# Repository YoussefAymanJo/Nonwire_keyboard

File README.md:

Nonwire_keyboard

## Description

Wireless Keyboarb based on split keyboard mechanism.As it consist of main keyboard  powered by rechargeable Battery which can operate up to week.And operated by nice Nano and soup display.The right part is Soup numpad,this numpad can operate up to week and soup friendly.
## Why it was built
I built this,beacause i always need mechanical keyboard,but i need to customize it features by myself.So this keyboard it custosmized to my needings.Also,it has customized features based on usage.Nonwire keyboard is not just regular keybaord but,desgined to be my companion.
## How to use it / Build it
Firsly,printing all 3d models after that fabricate PCB.After that assemble mx switches,MCU and battery management of pcb.then assemble all this parts together.finally,upload firmware on nice nano,the test all 
## Schematic
I made the schematic and keyboard matrix for the main keyboard, then the soup numpad the right part .

## PCB
I routed the pcb ,then i outlined the shape of keyboard and soup .

## CAD
I started   sketcking plat for main keyboard,the i the Enclosure , then the top cover.After that i worked on soup outlinne shape and assemble

 #### Soup 

## Firmware
I used kmk with circuit python as firmare,and make code for the left part which is keyboard and the right one the soup numpad

## BOM 
I made the BOM  and needed materials ,in egypt then convert its price to USD dollar.

## Zine

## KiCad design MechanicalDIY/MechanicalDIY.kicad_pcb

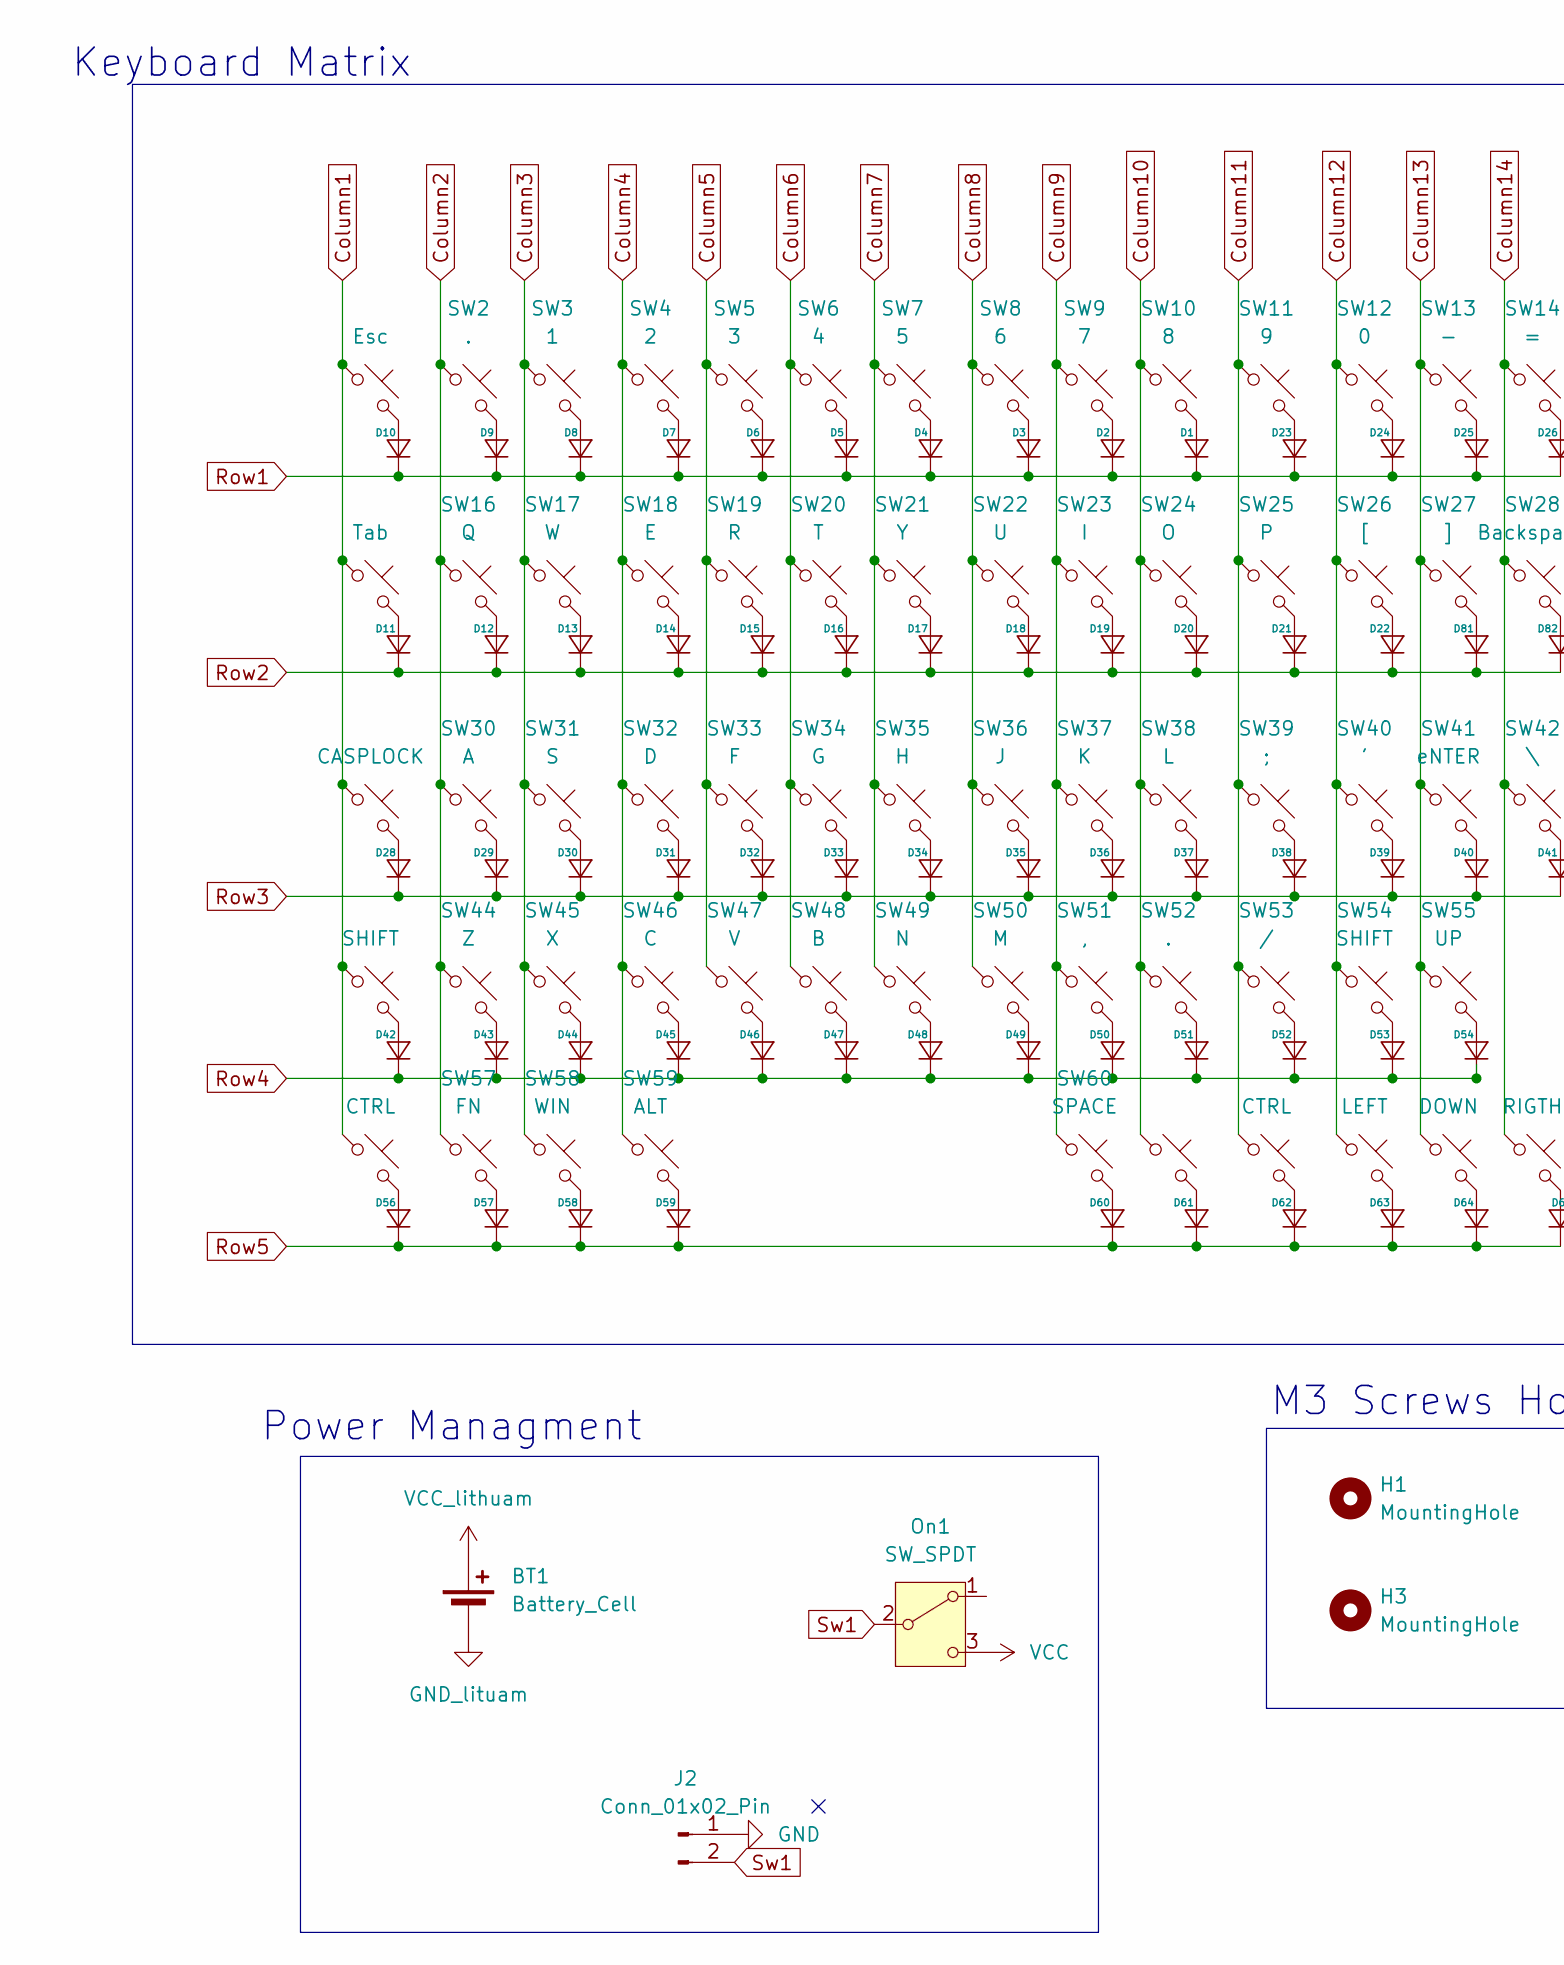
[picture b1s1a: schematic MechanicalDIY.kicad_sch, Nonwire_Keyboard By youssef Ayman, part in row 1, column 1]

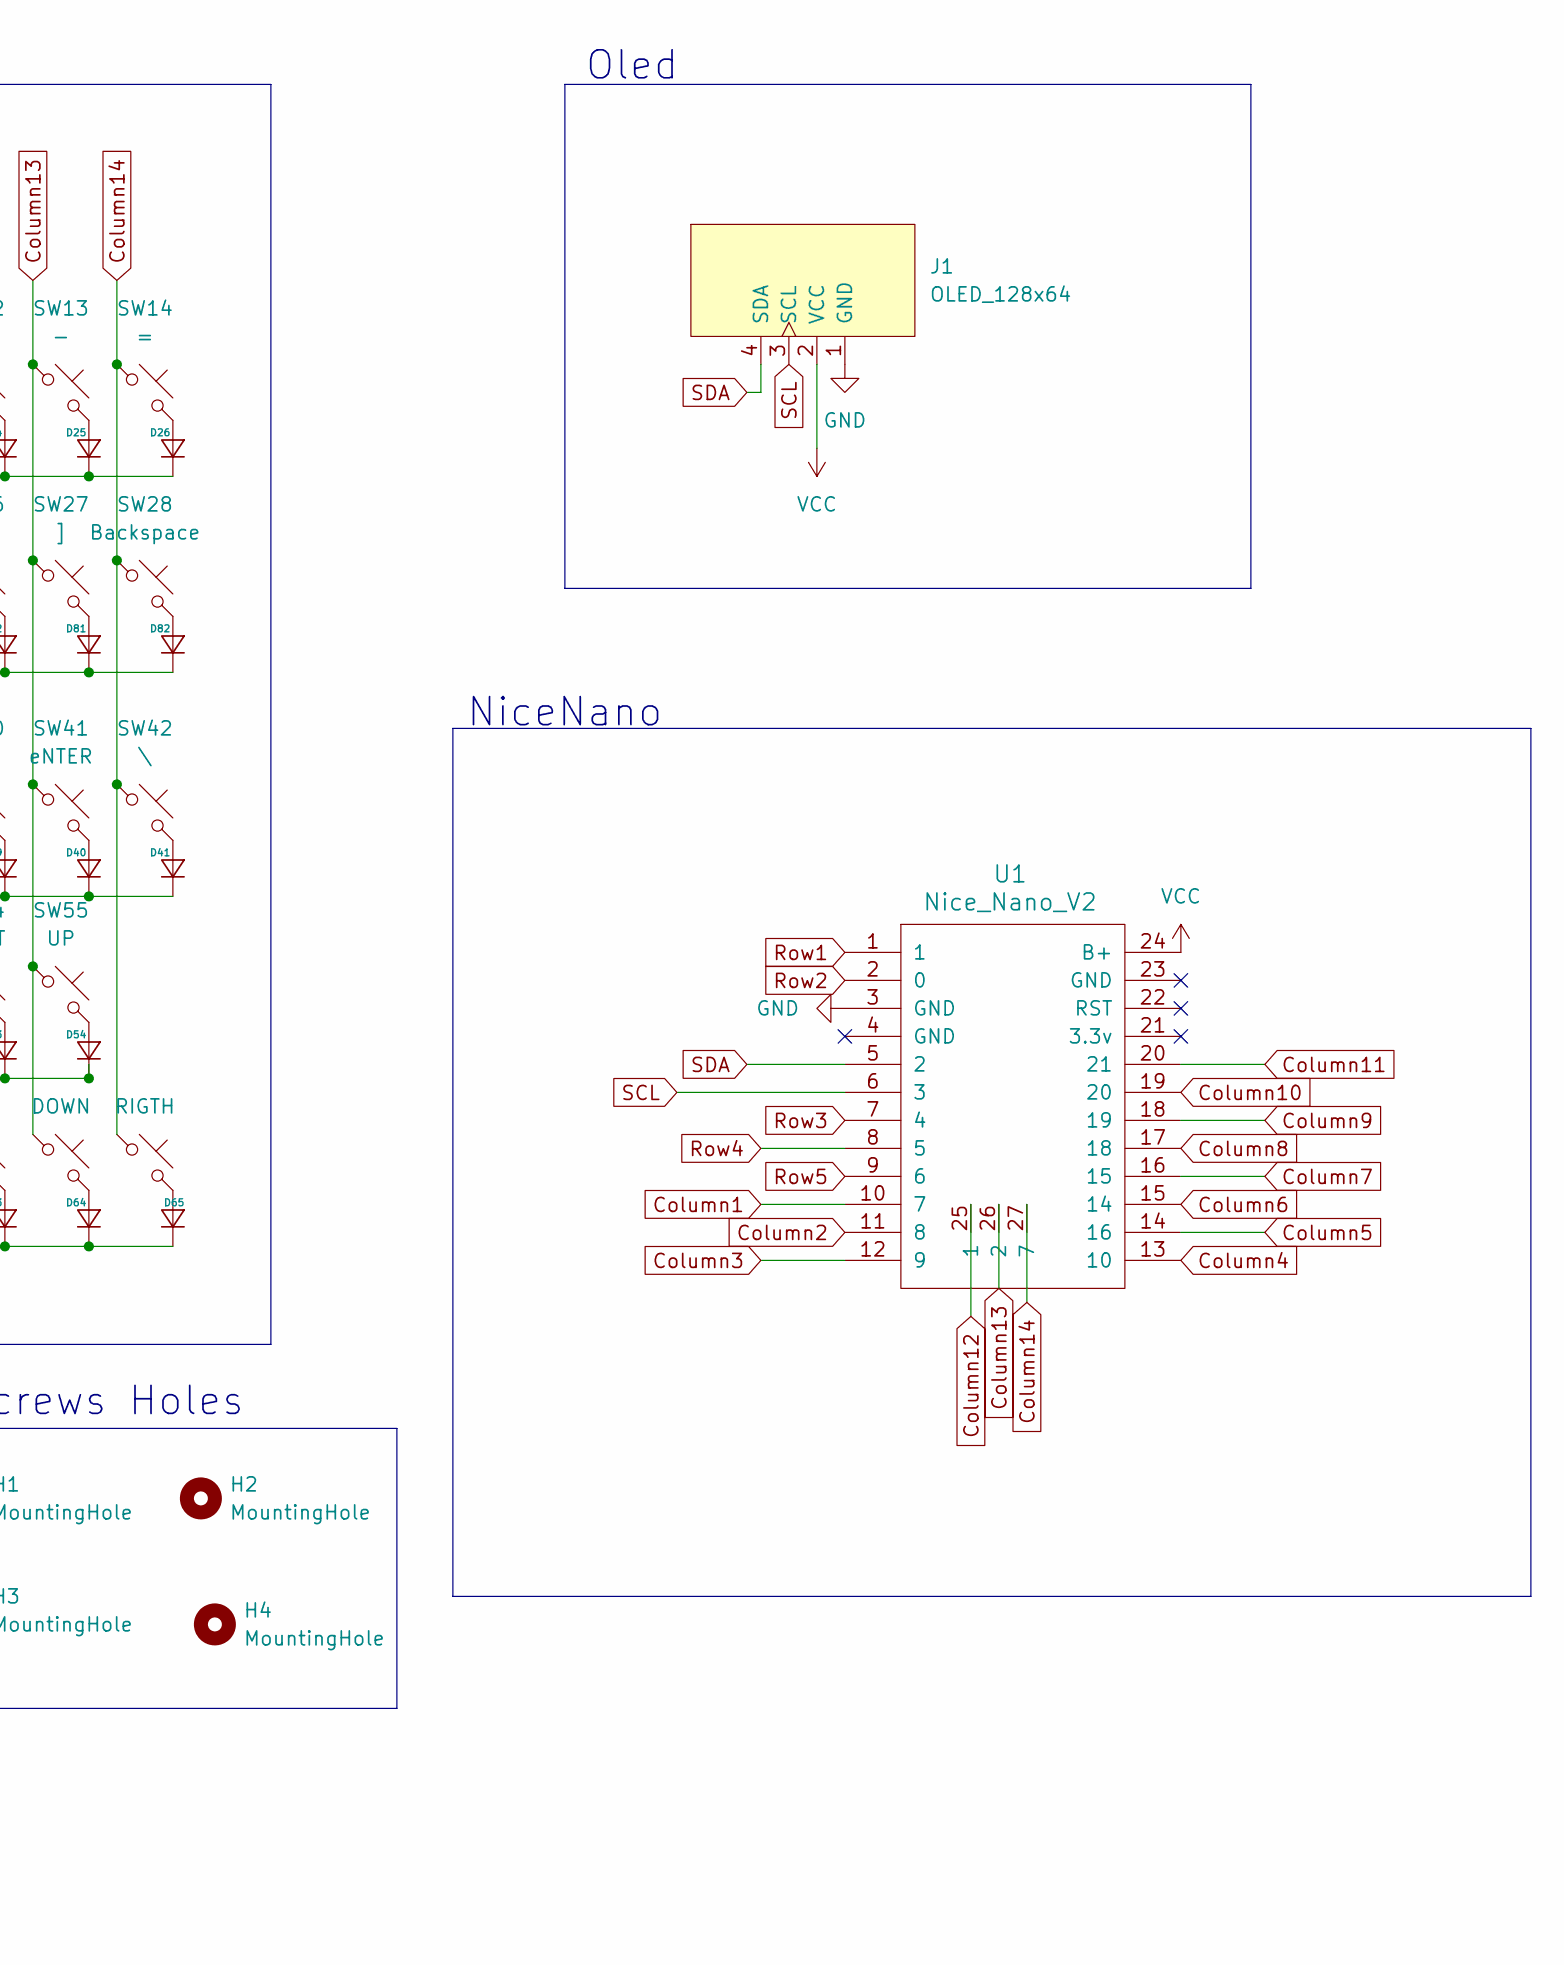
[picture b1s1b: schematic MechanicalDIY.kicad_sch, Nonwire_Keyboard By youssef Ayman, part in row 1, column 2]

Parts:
BT1: Battery_Cell
D1, D2, D3, D4, D5, D6, D7, D8, D9, D10, D11, D12, D13, D14, D15, D16, D17, D18, D19, D20, D21, D22, D23, D24, D25, D26, D28, D29, D30, D31, D32, D33, D34, D35, D36, D37, D38, D39, D40, D41, D42, D43, D44, D45, D46, D47, D48, D49, D50, D51, D52, D53, D54, D56, D57, D58, D59, D60, D61, D62, D63, D64, D65, D81, D82: Diode_DO-35
H1, H2, H3, H4: MountingHole; MountingHole_3.2mm_M3
J1: OLED_128x64
J2: Conn_01x02_Pin; JST_PH_S2B-PH-K_1x02_P2.00mm_Horizontal
On1: SW_SPDT; SW_Slide_SPDT_Angled_CK_OS102011MA1Q
SW1: Esc; MX_PCB_1.00u
SW2, SW52: .; MX_PCB_1.00u
SW3: 1; MX_PCB_1.00u
SW4: 2; MX_PCB_1.00u
SW5: 3; MX_PCB_1.00u
SW6: 4; MX_PCB_1.00u
SW7: 5; MX_PCB_1.00u
SW8: 6; MX_PCB_1.00u
SW9: 7; MX_PCB_1.00u
SW10: 8; MX_PCB_1.00u
SW11: 9; MX_PCB_1.00u
SW12: 0; MX_PCB_1.00u
SW13: -; MX_PCB_1.00u
SW14: =; MX_PCB_1.00u
SW15: Tab; MX_PCB_1.50u
SW16: Q; MX_PCB_1.00u
SW17: W; MX_PCB_1.00u
SW18: E; MX_PCB_1.00u
SW19: R; MX_PCB_1.00u
SW20: T; MX_PCB_1.00u
SW21: Y; MX_PCB_1.00u
SW22: U; MX_PCB_1.00u
SW23: I; MX_PCB_1.00u
SW24: O; MX_PCB_1.00u
SW25: P; MX_PCB_1.00u
SW26: [; MX_PCB_1.00u
SW27: ]; MX_PCB_1.00u
SW28: Backspace; MX_PCB_2.00u
SW29: CASPLOCK; MX_PCB_1.75u
SW30: A; MX_PCB_1.00u
SW31: S; MX_PCB_1.00u
SW32: D; MX_PCB_1.00u
SW33: F; MX_PCB_1.00u
SW34: G; MX_PCB_1.00u
SW35: H; MX_PCB_1.00u
SW36: J; MX_PCB_1.00u
SW37: K; MX_PCB_1.00u
SW38: L; MX_PCB_1.00u
SW39: ;; MX_PCB_1.00u
SW40: '; MX_PCB_1.00u
SW41: eNTER; MX_PCB_2.25u
SW42: \; MX_PCB_1.50u
SW43: SHIFT; MX_PCB_2.25u
SW44: Z; MX_PCB_1.00u
SW45: X; MX_PCB_1.00u
SW46: C; MX_PCB_1.00u
SW47: V; MX_PCB_1.00u
SW48: B; MX_PCB_1.00u
SW49: N; MX_PCB_1.00u
SW50: M; MX_PCB_1.00u
SW51: ,; MX_PCB_1.00u
SW53: /; MX_PCB_1.00u
SW54: SHIFT; MX_PCB_1.75u
SW55: UP; MX_PCB_1.00u
SW56: CTRL; MX_PCB_1.25u
SW57: FN; MX_PCB_1.25u
SW58: WIN; MX_PCB_1.25u
SW59: ALT; MX_PCB_6.25u
SW60: SPACE; MX_PCB_1.00u
SW61: ALT; MX_PCB_1.00u
SW62: CTRL; MX_PCB_1.00u
SW63: LEFT; MX_PCB_1.00u
SW64: DOWN; MX_PCB_1.00u
SW65: RIGTH; MX_PCB_1.00u
U1: Nice_Nano_V2

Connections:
Column1: SW1.1, SW15.1, SW29.1, SW43.1, SW56.1, U1.10 (7)
Column2: SW2.1, SW16.1, SW30.1, SW44.1, SW57.1, U1.11 (8)
Column3: SW3.1, SW17.1, SW31.1, SW45.1, SW58.1, U1.12 (9)
Column4: SW4.1, SW18.1, SW32.1, SW46.1, SW59.1, U1.13 (10)
Column5: SW5.1, SW19.1, SW33.1, SW47.1, U1.14 (16)
Column6: SW6.1, SW20.1, SW34.1, SW48.1, U1.15 (14)
Column7: SW7.1, SW21.1, SW35.1, SW49.1, U1.16 (15)
Column8: SW8.1, SW22.1, SW36.1, SW50.1, U1.17 (18)
Column9: SW9.1, SW23.1, SW37.1, SW51.1, SW60.1, U1.18 (19)
Column10: SW10.1, SW24.1, SW38.1, SW52.1, SW61.1, U1.19 (20)
Column11: SW11.1, SW25.1, SW39.1, SW53.1, SW62.1, U1.20 (21)
Column12: SW12.1, SW26.1, SW40.1, SW54.1, SW63.1, U1.25 (1)
Column13: SW13.1, SW27.1, SW41.1, SW55.1, SW64.1, U1.26 (2)
Column14: SW14.1, SW28.1, SW42.1, SW65.1, U1.27 (7)
GND: J1.1 (GND), J2.1, U1.3 (GND)
unnamed: D1.2 (A), SW10.2
unnamed: D2.2 (A), SW9.2
unnamed: D3.2 (A), SW8.2
unnamed: D4.2 (A), SW7.2
unnamed: D5.2 (A), SW6.2
unnamed: D6.2 (A), SW5.2
unnamed: D7.2 (A), SW4.2
unnamed: D8.2 (A), SW3.2
unnamed: D9.2 (A), SW2.2
unnamed: D10.2 (A), SW1.2
unnamed: D11.2 (A), SW15.2
unnamed: D12.2 (A), SW16.2
unnamed: D13.2 (A), SW17.2
unnamed: D14.2 (A), SW18.2
unnamed: D15.2 (A), SW19.2
unnamed: D16.2 (A), SW20.2
unnamed: D17.2 (A), SW21.2
unnamed: D18.2 (A), SW22.2
unnamed: D19.2 (A), SW23.2
unnamed: D20.2 (A), SW24.2
unnamed: D21.2 (A), SW25.2
unnamed: D22.2 (A), SW26.2
unnamed: D23.2 (A), SW11.2
unnamed: D24.2 (A), SW12.2
unnamed: D25.2 (A), SW13.2
unnamed: D26.2 (A), SW14.2
unnamed: D28.2 (A), SW29.2
unnamed: D29.2 (A), SW30.2
unnamed: D30.2 (A), SW31.2
unnamed: D31.2 (A), SW32.2
unnamed: D32.2 (A), SW33.2
unnamed: D33.2 (A), SW34.2
unnamed: D34.2 (A), SW35.2
unnamed: D35.2 (A), SW36.2
unnamed: D36.2 (A), SW37.2
unnamed: D37.2 (A), SW38.2
unnamed: D38.2 (A), SW39.2
unnamed: D39.2 (A), SW40.2
unnamed: D40.2 (A), SW41.2
unnamed: D41.2 (A), SW42.2
unnamed: D42.2 (A), SW43.2
unnamed: D43.2 (A), SW44.2
unnamed: D44.2 (A), SW45.2
unnamed: D45.2 (A), SW46.2
unnamed: D46.2 (A), SW47.2
unnamed: D47.2 (A), SW48.2
unnamed: D48.2 (A), SW49.2
unnamed: D49.2 (A), SW50.2
unnamed: D50.2 (A), SW51.2
unnamed: D51.2 (A), SW52.2
unnamed: D52.2 (A), SW53.2
unnamed: D53.2 (A), SW54.2
unnamed: D54.2 (A), SW55.2
unnamed: D56.2 (A), SW56.2
unnamed: D57.2 (A), SW57.2
unnamed: D58.2 (A), SW58.2
unnamed: D59.2 (A), SW59.2
unnamed: D60.2 (A), SW60.2
unnamed: D61.2 (A), SW61.2
unnamed: D62.2 (A), SW62.2
unnamed: D63.2 (A), SW63.2
unnamed: D64.2 (A), SW64.2
unnamed: D65.2 (A), SW65.2
unnamed: D81.2 (A), SW27.2
unnamed: D82.2 (A), SW28.2
Row1: D1.1 (K), D2.1 (K), D3.1 (K), D4.1 (K), D5.1 (K), D6.1 (K), D7.1 (K), D8.1 (K), D9.1 (K), D10.1 (K), D23.1 (K), D24.1 (K), D25.1 (K), D26.1 (K), U1.1
Row2: D11.1 (K), D12.1 (K), D13.1 (K), D14.1 (K), D15.1 (K), D16.1 (K), D17.1 (K), D18.1 (K), D19.1 (K), D20.1 (K), D21.1 (K), D22.1 (K), D81.1 (K), D82.1 (K), U1.2 (0)
Row3: D28.1 (K), D29.1 (K), D30.1 (K), D31.1 (K), D32.1 (K), D33.1 (K), D34.1 (K), D35.1 (K), D36.1 (K), D37.1 (K), D38.1 (K), D39.1 (K), D40.1 (K), D41.1 (K), U1.7 (4)
Row4: D42.1 (K), D43.1 (K), D44.1 (K), D45.1 (K), D46.1 (K), D47.1 (K), D48.1 (K), D49.1 (K), D50.1 (K), D51.1 (K), D52.1 (K), D53.1 (K), D54.1 (K), U1.8 (5)
Row5: D56.1 (K), D57.1 (K), D58.1 (K), D59.1 (K), D60.1 (K), D61.1 (K), D62.1 (K), D63.1 (K), D64.1 (K), D65.1 (K), U1.9 (6)
SCL: J1.3 (SCL), U1.6 (3)
SDA: J1.4 (SDA), U1.5 (2)
Sw1: J2.2, On1.2 (B)
VCC: J1.2 (VCC), On1.3 (C), U1.24 (B+)

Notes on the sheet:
M3 Screws Holes
NiceNano
Oled
Power Managment
Keyboard Matrix

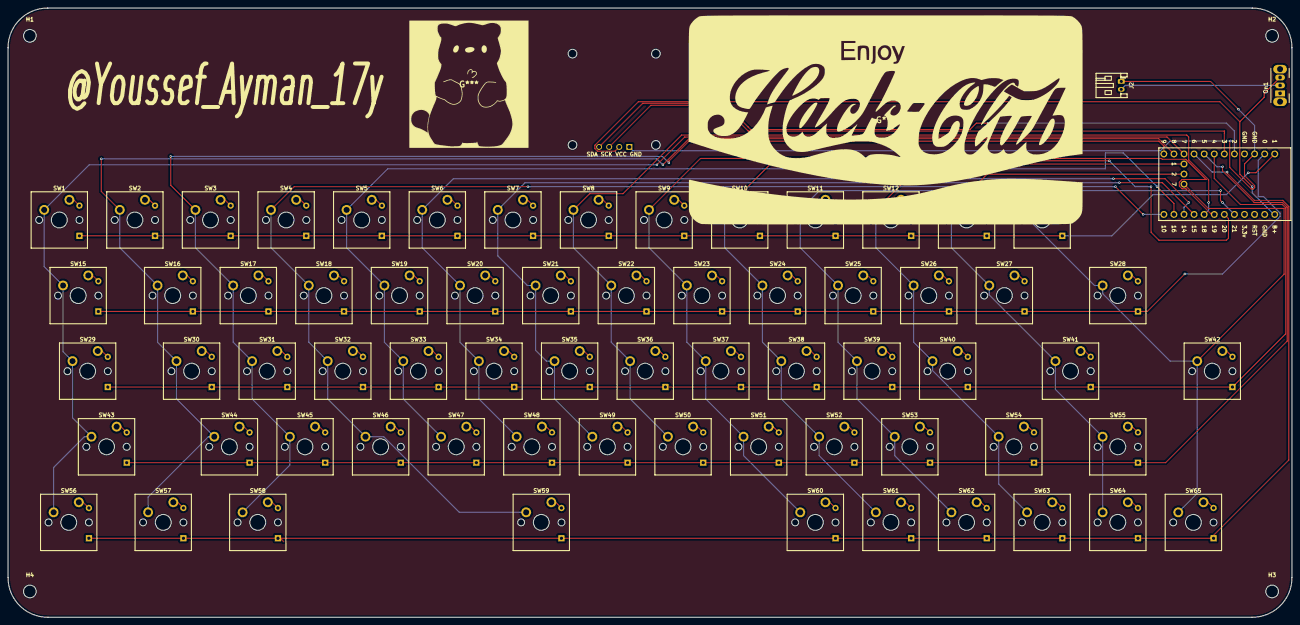
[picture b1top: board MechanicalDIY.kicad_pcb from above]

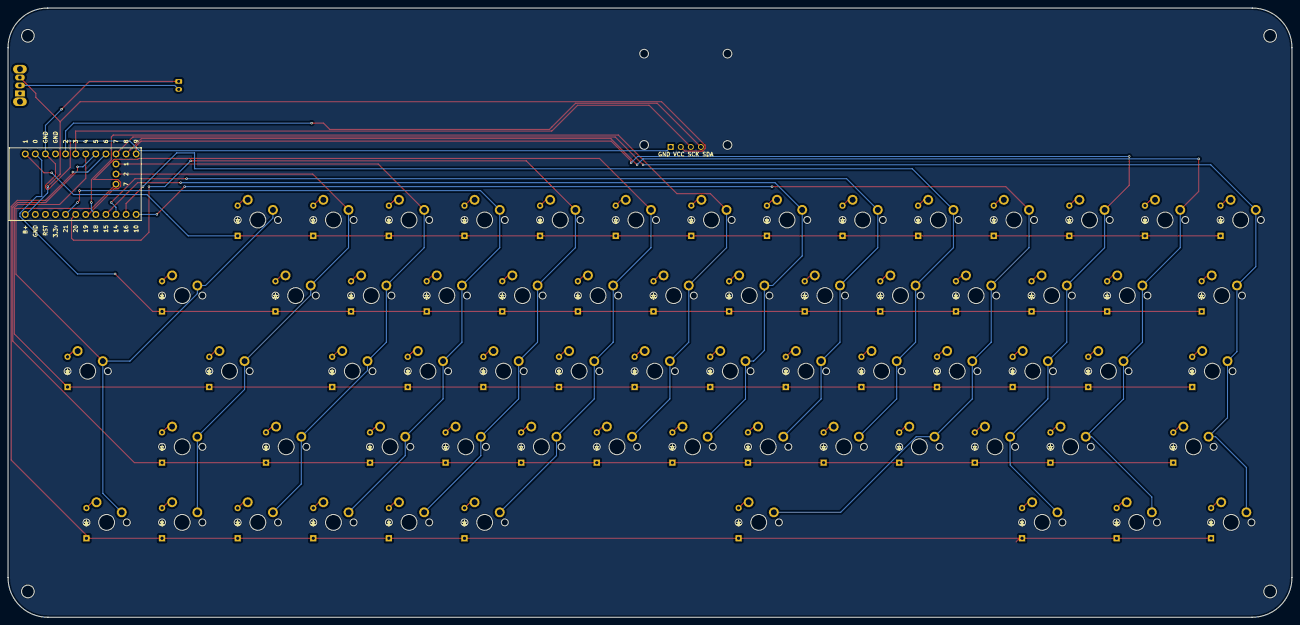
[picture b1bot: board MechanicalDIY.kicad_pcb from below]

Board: 2 copper layers, 323.5 x 153.5 mm, 138 parts (65 on the bottom side), 89 nets.

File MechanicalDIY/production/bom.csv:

Designator,Footprint,Quantity,Value,LCSC Part #
"D1, D10, D11, D12, D13, D14, D15, D16, D17, D18, D19, D2, D20, D21, D22, D23, D24, D25, D26, D28, D29, D3, D30, D31, D32, D33, D34, D35, D36, D37, D38, D39, D4, D40, D41, D42, D43, D44, D45, D46, D47, D48, D49, D5, D50, D51, D52, D53, D54, D56, D57, D58, D59, D6, D60, D61, D62, D63, D64, D65, D7, D8, D81, D82, D9",Diode_DO-35,65,~,
J1,OLED_128x64,1,OLED_128x64,
J2,JST_PH_S2B-PH-K_1x02_P2.00mm_Horizontal,1,Conn_01x02_Pin,
ON1,SW_Slide_SPDT_Angled_CK_OS102011MA1Q,1,SW_SPDT,
SW1,MX_PCB_1.00u,1,Esc,
SW10,MX_PCB_1.00u,1,8,
SW11,MX_PCB_1.00u,1,9,
SW12,MX_PCB_1.00u,1,0,
SW13,MX_PCB_1.00u,1,-,
SW14,MX_PCB_1.00u,1,=,
SW15,MX_PCB_1.50u,1,Tab,
SW16,MX_PCB_1.00u,1,Q,
SW17,MX_PCB_1.00u,1,W,
SW18,MX_PCB_1.00u,1,E,
SW19,MX_PCB_1.00u,1,R,
"SW2, SW52",MX_PCB_1.00u,2,.,
SW20,MX_PCB_1.00u,1,T,
SW21,MX_PCB_1.00u,1,Y,
SW22,MX_PCB_1.00u,1,U,
SW23,MX_PCB_1.00u,1,I,
SW24,MX_PCB_1.00u,1,O,
SW25,MX_PCB_1.00u,1,P,
SW26,MX_PCB_1.00u,1,[,
SW27,MX_PCB_1.00u,1,],
SW28,MX_PCB_2.00u,1,Backspace,
SW29,MX_PCB_1.75u,1,CASPLOCK,
SW3,MX_PCB_1.00u,1,1,
SW30,MX_PCB_1.00u,1,A,
SW31,MX_PCB_1.00u,1,S,
SW32,MX_PCB_1.00u,1,D,
SW33,MX_PCB_1.00u,1,F,
SW34,MX_PCB_1.00u,1,G,
SW35,MX_PCB_1.00u,1,H,
SW36,MX_PCB_1.00u,1,J,
SW37,MX_PCB_1.00u,1,K,
SW38,MX_PCB_1.00u,1,L,
SW39,MX_PCB_1.00u,1,;,
SW4,MX_PCB_1.00u,1,2,
SW40,MX_PCB_1.00u,1,',
SW41,MX_PCB_2.25u,1,eNTER,
SW42,MX_PCB_1.50u,1,\,
SW43,MX_PCB_2.25u,1,SHIFT,
SW44,MX_PCB_1.00u,1,Z,
SW45,MX_PCB_1.00u,1,X,
SW46,MX_PCB_1.00u,1,C,
SW47,MX_PCB_1.00u,1,V,
SW48,MX_PCB_1.00u,1,B,
SW49,MX_PCB_1.00u,1,N,
SW5,MX_PCB_1.00u,1,3,
SW50,MX_PCB_1.00u,1,M,
SW51,MX_PCB_1.00u,1,",",
SW53,MX_PCB_1.00u,1,/,
SW54,MX_PCB_1.75u,1,SHIFT,
SW55,MX_PCB_1.00u,1,UP,
SW56,MX_PCB_1.25u,1,CTRL,
SW57,MX_PCB_1.25u,1,FN,
SW58,MX_PCB_1.25u,1,WIN,
SW59,MX_PCB_6.25u,1,ALT,
SW6,MX_PCB_1.00u,1,4,
SW60,MX_PCB_1.00u,1,SPACE,
SW61,MX_PCB_1.00u,1,ALT,
SW62,MX_PCB_1.00u,1,CTRL,
SW63,MX_PCB_1.00u,1,LEFT,
SW64,MX_PCB_1.00u,1,DOWN,
SW65,MX_PCB_1.00u,1,RIGTH,
SW7,MX_PCB_1.00u,1,5,
SW8,MX_PCB_1.00u,1,6,
SW9,MX_PCB_1.00u,1,7,
U1,Nice_Nano_V2,1,Nice_Nano_V2,

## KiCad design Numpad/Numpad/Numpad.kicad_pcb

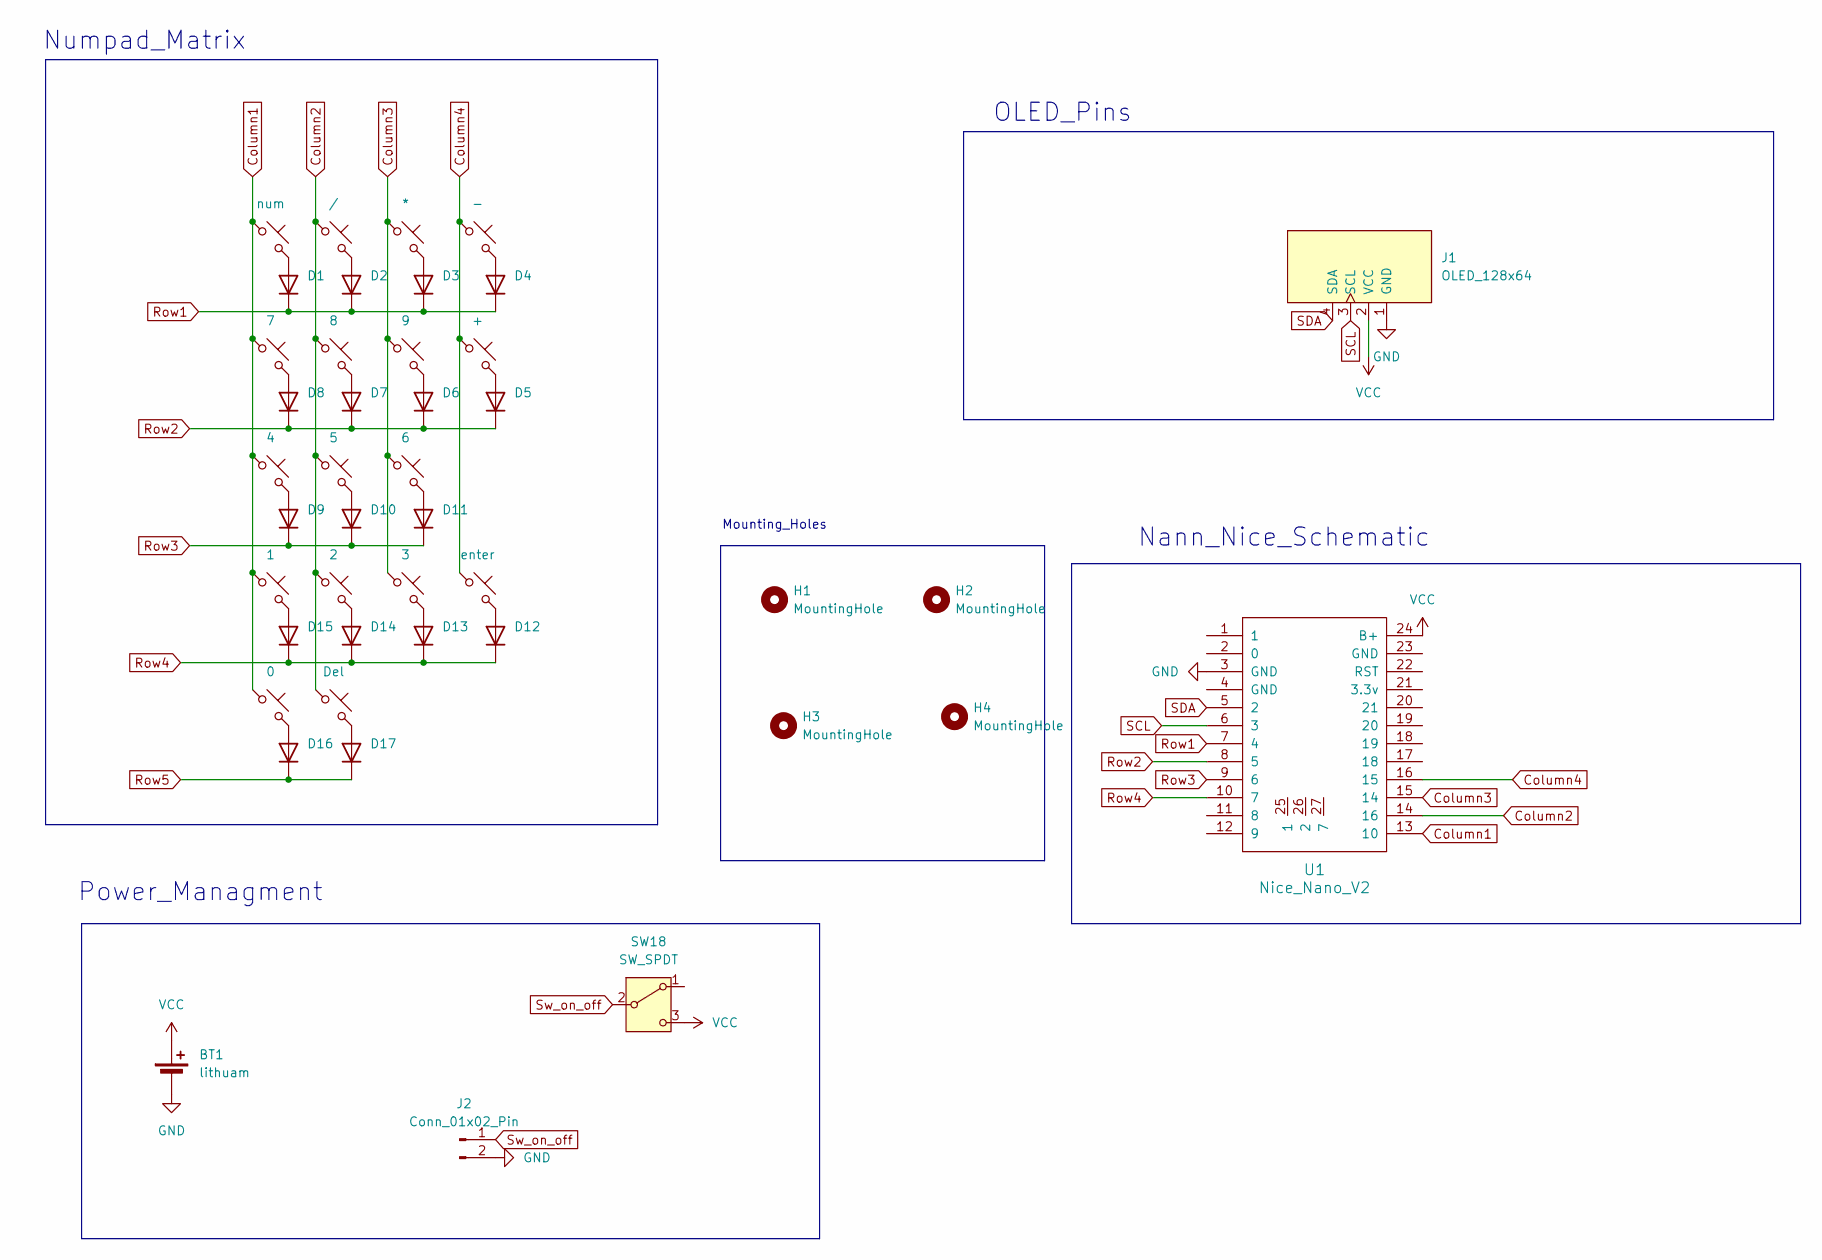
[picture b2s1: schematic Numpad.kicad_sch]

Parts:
BT1: lithuam
D1, D2, D3, D4, D5, D6, D7, D8, D9, D10, D11, D12, D13, D14, D15, D16, D17: 1N4148WT; Diode_DO-35
H1, H2, H3, H4: MountingHole; MountingHole_3.2mm_M3
J1: OLED_128x64
J2: Conn_01x02_Pin; JST_PH_S2B-PH-K_1x02_P2.00mm_Horizontal
SW1: num; MX_PCB_1.00u
SW2: /; MX_PCB_1.00u
SW3: *; MX_PCB_1.00u
SW4: -; MX_PCB_1.00u
SW5: 7; MX_PCB_1.00u
SW6: 8; MX_PCB_1.00u
SW7: 9; MX_PCB_1.00u
SW8: +; MX_PCB_2.00u
SW9: 4; MX_PCB_1.00u
SW10: 5; MX_PCB_1.00u
SW11: 6; MX_PCB_1.00u
SW12: 1; MX_PCB_1.00u
SW13: 2; MX_PCB_1.00u
SW14: 3; MX_PCB_1.00u
SW15: enter; MX_PCB_2.00u
SW16: Del; MX_PCB_1.00u
SW17: 0; MX_PCB_2.00u
SW18: SW_SPDT; SW_Slide_SPDT_Angled_CK_OS102011MA1Q
U1: Nice_Nano_V2

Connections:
Column1: SW1.1, SW5.1, SW9.1, SW12.1, SW17.1, U1.13 (10)
Column2: SW2.1, SW6.1, SW10.1, SW13.1, SW16.1, U1.14 (16)
Column3: SW3.1, SW7.1, SW11.1, SW14.1, U1.15 (14)
Column4: SW4.1, SW8.1, SW15.1, U1.16 (15)
GND: BT1.2 (-), J1.1 (GND), J2.2, U1.3 (GND)
unnamed: D1.2 (A), SW1.2
unnamed: D2.2 (A), SW2.2
unnamed: D3.2 (A), SW3.2
unnamed: D4.2 (A), SW4.2
unnamed: D5.2 (A), SW8.2
unnamed: D6.2 (A), SW7.2
unnamed: D7.2 (A), SW6.2
unnamed: D8.2 (A), SW5.2
unnamed: D9.2 (A), SW9.2
unnamed: D10.2 (A), SW10.2
unnamed: D11.2 (A), SW11.2
unnamed: D12.2 (A), SW15.2
unnamed: D13.2 (A), SW14.2
unnamed: D14.2 (A), SW13.2
unnamed: D15.2 (A), SW12.2
unnamed: D16.2 (A), SW17.2
unnamed: D17.2 (A), SW16.2
Row1: D1.1 (K), D2.1 (K), D3.1 (K), D4.1 (K), U1.7 (4)
Row2: D5.1 (K), D6.1 (K), D7.1 (K), D8.1 (K), U1.8 (5)
Row3: D9.1 (K), D10.1 (K), D11.1 (K), U1.9 (6)
Row4: D12.1 (K), D13.1 (K), D14.1 (K), D15.1 (K), U1.10 (7)
Row5: D16.1 (K), D17.1 (K)
SCL: J1.3 (SCL), U1.6 (3)
SDA: J1.4 (SDA), U1.5 (2)
Sw_on_off: J2.1, SW18.2 (B)
VCC: BT1.1 (+), J1.2 (VCC), SW18.3 (C), U1.24 (B+)

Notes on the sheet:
Numpad_Matrix
Mounting_Holes
Nann_Nice_Schematic
Power_Managment
OLED_Pins

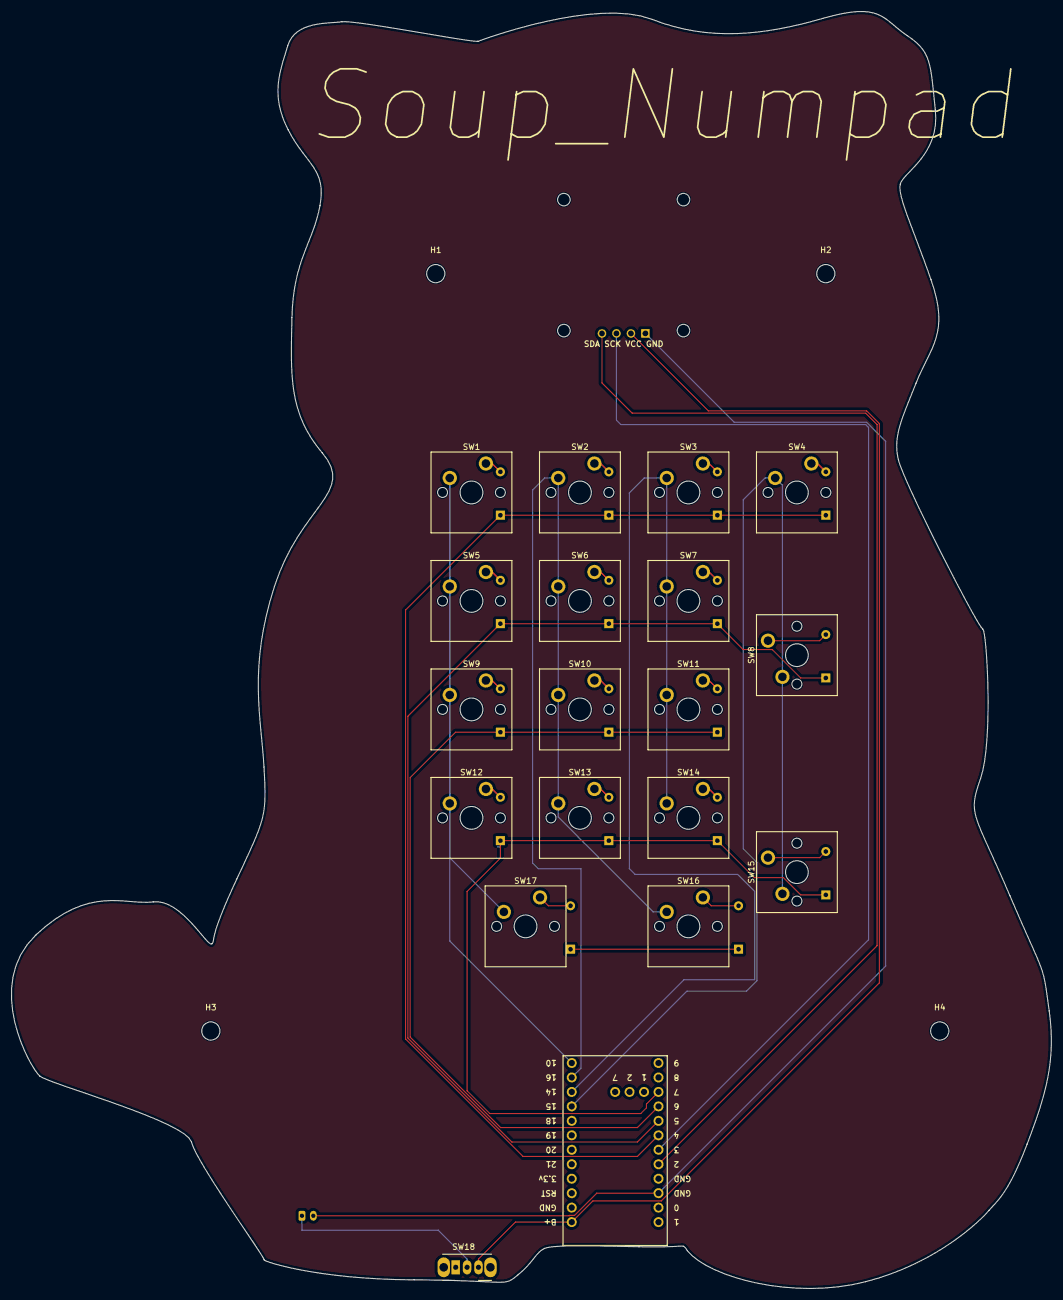
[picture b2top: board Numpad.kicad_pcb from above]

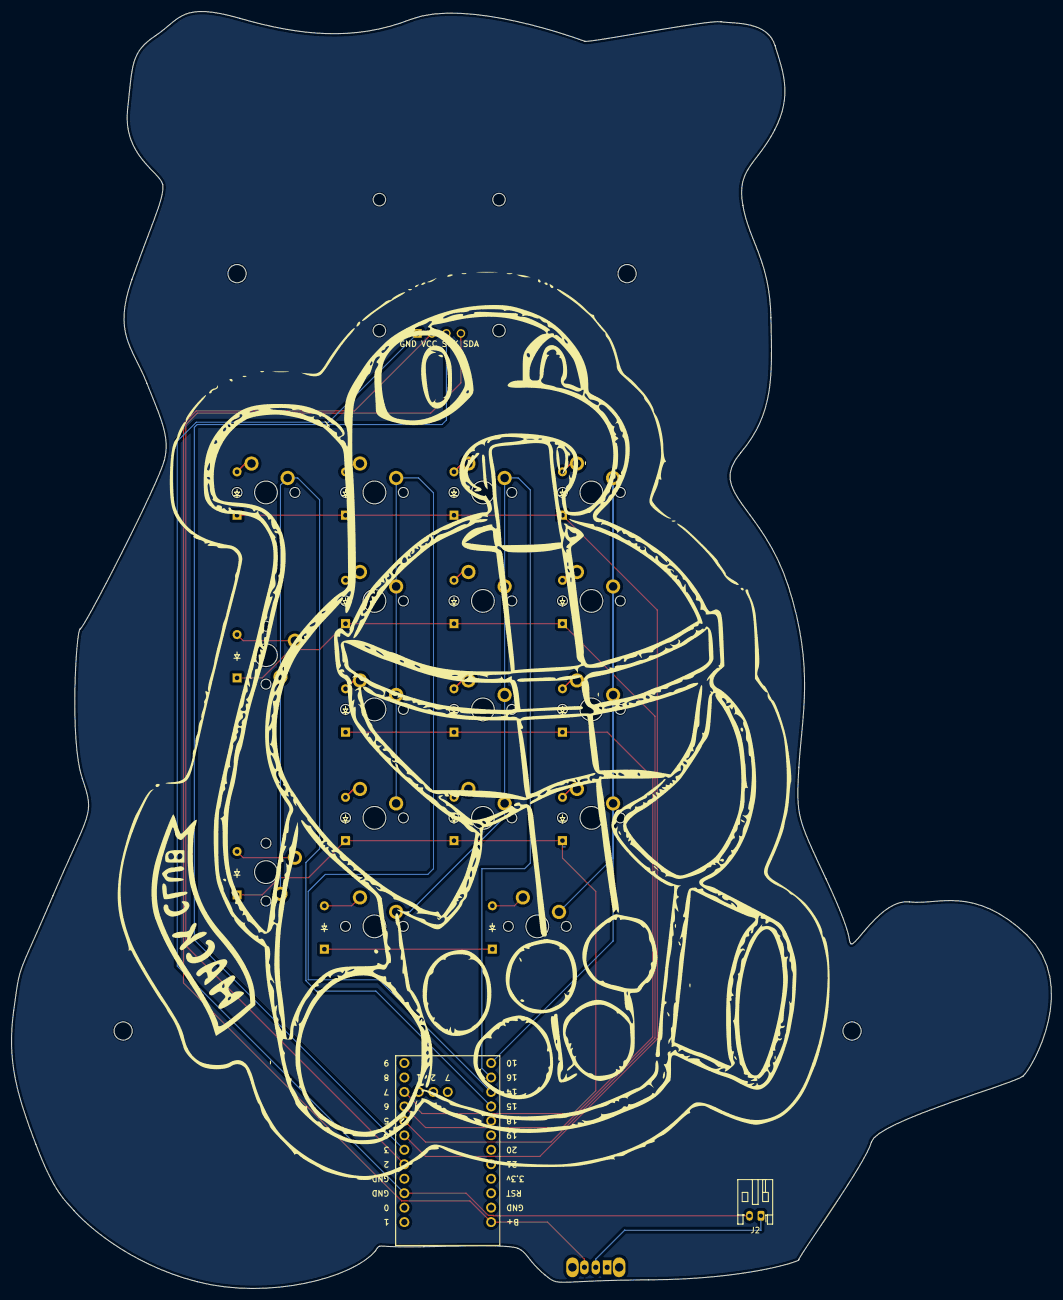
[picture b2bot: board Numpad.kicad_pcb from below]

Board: 2 copper layers, 182.6 x 224.2 mm, 42 parts (18 on the bottom side), 31 nets.

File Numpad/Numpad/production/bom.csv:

Designator,Footprint,Quantity,Value,LCSC Part #
"D1, D10, D11, D12, D13, D14, D15, D16, D17, D2, D3, D4, D5, D6, D7, D8, D9",Diode_DO-35,17,1N4148WT,
J1,OLED_128x64,1,OLED_128x64,
J2,JST_PH_S2B-PH-K_1x02_P2.00mm_Horizontal,1,Conn_01x02_Pin,
SW1,MX_PCB_1.00u,1,num,
SW10,MX_PCB_1.00u,1,5,
SW11,MX_PCB_1.00u,1,6,
SW12,MX_PCB_1.00u,1,1,
SW13,MX_PCB_1.00u,1,2,
SW14,MX_PCB_1.00u,1,3,
SW15,MX_PCB_2.00u,1,enter,
SW16,MX_PCB_1.00u,1,Del,
SW17,MX_PCB_2.00u,1,0,
SW18,SW_Slide_SPDT_Angled_CK_OS102011MA1Q,1,SW_SPDT,
SW2,MX_PCB_1.00u,1,/,
SW3,MX_PCB_1.00u,1,*,
SW4,MX_PCB_1.00u,1,-,
SW5,MX_PCB_1.00u,1,7,
SW6,MX_PCB_1.00u,1,8,
SW7,MX_PCB_1.00u,1,9,
SW8,MX_PCB_2.00u,1,+,
SW9,MX_PCB_1.00u,1,4,
U1,Nice_Nano_V2,1,Nice_Nano_V2,

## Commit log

2026-06-12 udoate
